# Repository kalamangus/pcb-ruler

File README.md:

# pcb-ruler
PCB ruler with a wide variety of symbols including style elements.

# images

# attribution

This project uses elements adapted from [PCBruler by jbtronics](https://github.com/jbtronics/PCBruler),  
licensed under [Creative Commons Attribution 4.0 International (CC BY 4.0)]([https://creativecommons.org/licenses/by/4.0/](https://github.com/jbtronics/PCBruler/blob/master/License.md)).

# To add
USB-A pinout

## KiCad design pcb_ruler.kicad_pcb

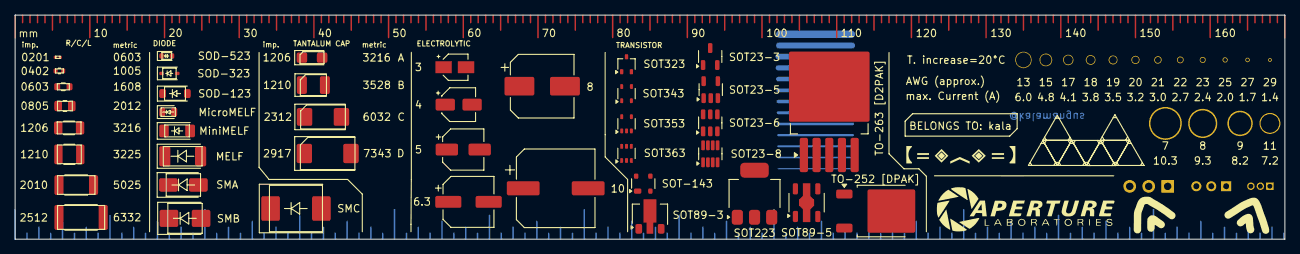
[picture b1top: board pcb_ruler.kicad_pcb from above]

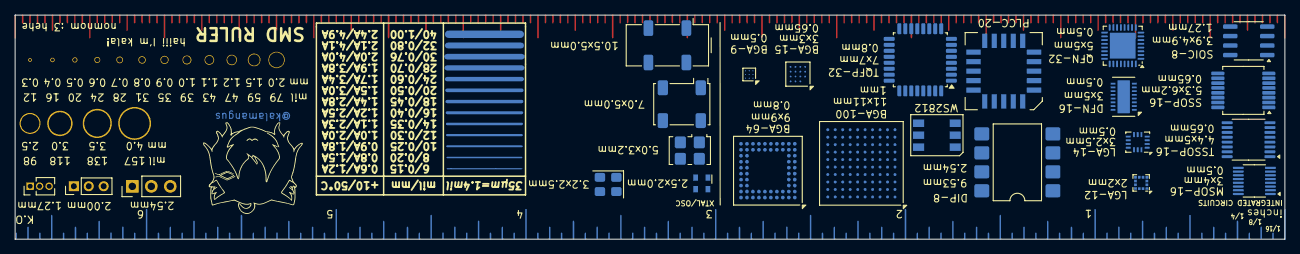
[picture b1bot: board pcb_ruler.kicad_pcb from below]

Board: 4 copper layers, 170.0 x 30.0 mm, 65 parts (24 on the bottom side), 10 nets.

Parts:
0201: 0201; R_0201_0603Metric
0402: 0402; R_0402_1005Metric
0603: 0603; R_0603_1608Metric
0805: 0805; R_0805_2012Metric
1206: 1206; R_1206_3216Metric
1210: 1210; R_1210_3225Metric
2010: 2010; R_2010_5025Metric
2512: 2512; R_2512_6332Metric
C1: C_Polarized; CP_Elec_8x5.4
C2: C_Polarized; CP_EIA-3216-18_Kemet-A
C3: C_Polarized; CP_EIA-3528-21_Kemet-B
C4: C_Polarized; CP_EIA-6032-28_Kemet-C
C5: C_Polarized; CP_EIA-7343-31_Kemet-D
C7: C_Polarized; CP_Elec_3x5.3
C8: C_Polarized; CP_Elec_4x3
C9: C_Polarized; CP_Elec_5x3
C10: C_Polarized; CP_Elec_6.3x3.9
C12: C_Polarized; CP_Elec_10x7.7
D1: BAS16W; SOT-323_SC-70
D2: WS2812; LED_WS2812_PLCC6_5.0x5.0mm_P1.6mm
J1: Conn_01x03_Pin; PinHeader_1x03_P1.27mm_Vertical
J2: Conn_01x03_Pin; PinHeader_1x03_P2.00mm_Vertical
J3: Conn_01x03_Pin; PinHeader_1x03_P2.54mm_Vertical
MELF1: SMZxxx; D_MELF
MicroMELF1: BAV300; D_MicroMELF
MiniMELF1: BZV55B2V4; D_MiniMELF
Q1: BC817; SOT-23-3
Q2: DMMT5401; SOT-23-6
SMA1: SMAJ5.0A; D_SMA
SMB1: Z2SMBxxx; D_SMB
SMC1: MBRS340; D_SMC
SOD-123: MBR0520; D_SOD-123
SOD-323: SD05_SOD323; D_SOD-323
SOD-523: 1N4148WT; D_SOD-523
U1: LP2985-1.8; SOT-23-5
U2: INA241A1xDDF; SOT-23-8
U3: APE8865U4-12-HF-3; SOT-343_SC-70-4
U4: TLV70012_SOT353; SOT-353_SC-70-5
U5: TC7PZ14FU; SOT-363_SC-70-6
U6: MAX6816; SOT-143
U7: LM317L_SOT-89; SOT-89-3
U8: IS31LT3360; SOT-89-5
U9: LD1117S18TR_SOT223; SOT-223-3_TabPin2
U10: LM317_TO-252; TO-252-2
U11: IFX25401TBV50; TO-263-5_TabPin3
U12: ATtiny20-CC; UFBGA-15_3.0x3.0mm_Layout4x4_P0.65mm
U13: LTC4364CMS; MSOP-16_3x4.039mm_P0.5mm
U14: XPT2046TS; TSSOP-16_4.4x5mm_P0.65mm
U15: 74HC137; SSOP-16_5.3x6.2mm_P0.65mm
U16: SN65HVD255D; SOIC-8_3.9x4.9mm_P1.27mm
U17: 6N135S; SMDIP-8_W9.53mm
U18: LTC6082xDHC; DFN-16-1EP_3x5mm_P0.5mm_EP1.66x4.4mm
U19: TAS5825MRHB; Texas_RHB0032E_VQFN-32-1EP_5x5mm_P0.5mm_EP3.45x3.45mm_Therm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
U20: ATmega8-16A; TQFP-32_7x7mm_P0.8mm
U21: AD9891; BGA-64_9.0x9.0mm_Layout10x10_P0.8mm
U22: LM3914V; PLCC-20
U23: BMI160; Bosch_LGA-14_3x2.5mm_P0.5mm
U24: LM4990ITL; Texas_DSBGA-9_1.4715x1.4715mm_Layout3x3_P0.5mm
U25: LIS2MDL; LGA-12_2x2mm_P0.5mm
U26: EPM240F100; BGA-100_11.0x11.0mm_Layout10x10_P1.0mm_Ball0.5mm_Pad0.4mm_N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
Y1: ASDMB-xxxMHz; Oscillator_SMD_Abracon_ASDMB-4Pin_2.5x2.0mm
Y2: SiT8008xx-2x-xxE; Oscillator_SMD_SiT_PQFN-4Pin_3.2x2.5mm
Y3: SiT8008xx-3x-xxE; Oscillator_SMD_SiT_PQFN-4Pin_5.0x3.2mm
Y4: DFA-S11; Oscillator_SMD_Fordahl_DFAS11-4Pin_7.0x5.0mm
Y5: SG-8002JC; Oscillator_SMD_SeikoEpson_SG8002JC-4Pin_10.5x5.0mm

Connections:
unnamed: U2.2 (GND), U2.4 (GND)
unnamed: U5.2 (GND), U6.4 (VCC)
unnamed: U12.D2 (GND), U12.D3 (GND)
unnamed: U19.25 (PGND), U19.26 (PGND), U19.31 (PGND), U19.32 (PGND)
unnamed: U19.3 (PVDD), U19.4 (PVDD), U19.21 (PVDD), U19.22 (PVDD)
unnamed: U20.3 (GND), U20.5 (GND)
unnamed: U20.4 (VCC), U20.6 (VCC)
unnamed: U24.B1 (GND), U24.B2 (GND)
unnamed: U25.6 (GND), U25.8 (GND)
unnamed: Y2.2 (GND), Y5.4 (Vcc)

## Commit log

2025-06-25 File upload v1
    First ingest
2025-06-25 images for later use
2025-09-11 fixed files for package SOT23-5
2025-09-11 Deletion to swap for updated images
2025-09-11 Rename export/PCB-back.png to export/images/PCB-back.png
2025-09-11 Rename export/PCB-front.png to export/images/PCB-front.png
2025-09-11 Rename export/pcb-view-all.png to export/images/pcb-view-all.png
2025-09-11 Rename export/pcb-view-back.png to export/images/pcb-view-back.png
2025-09-11 Rename export/pcb-view-front.png to export/images/pcb-view-front.png
2025-09-11 Rename export/pcb_ruler_170.0x30.0mm_for_JLCPCB.zip to export/jlcpcb_gerber/pcb_ruler_170.0x30.0mm_for_JLCPCB.zip
2025-09-11 Rename export/pcb-views.pdf to export/images/pcb-views.pdf
2025-09-11 Rename export/schematic-view-plotted.pdf to export/images/schematic-view-plotted.pdf
2025-09-11 Rename export/pcb_ruler.kicad_pro to pcb_ruler.kicad_pro
